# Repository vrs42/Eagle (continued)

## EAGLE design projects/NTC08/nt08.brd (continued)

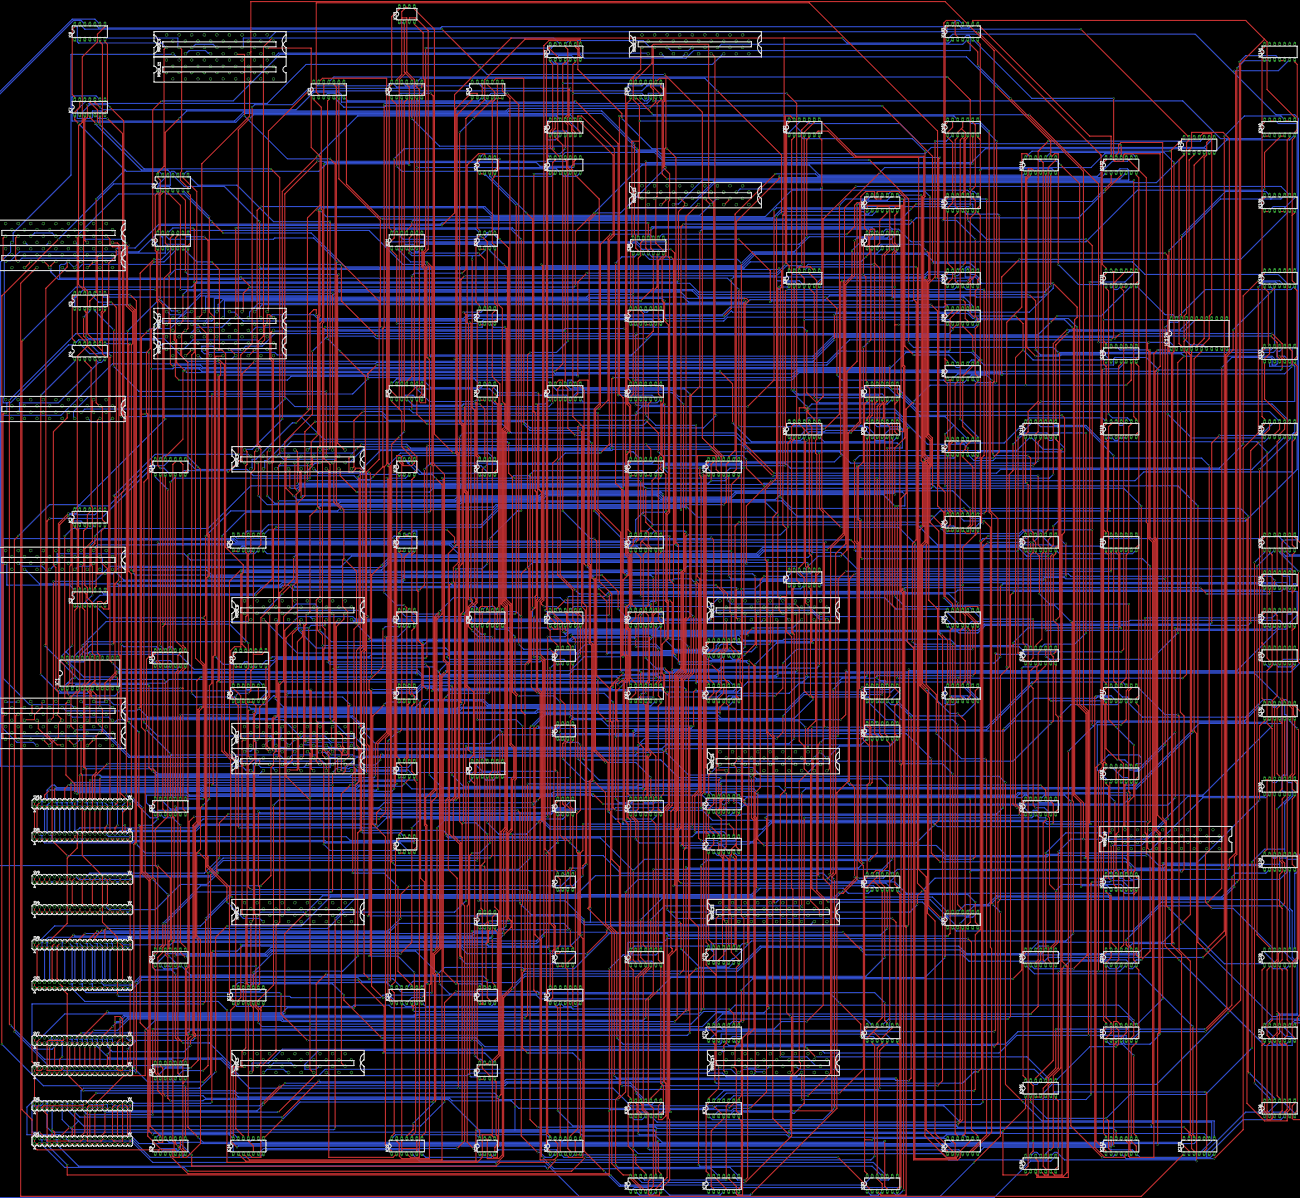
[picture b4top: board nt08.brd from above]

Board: 2 copper layers, 174 parts (0 on the bottom side), 550 nets.

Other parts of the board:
M916_11: W032; H807@1
M916_18: M228; H807@1

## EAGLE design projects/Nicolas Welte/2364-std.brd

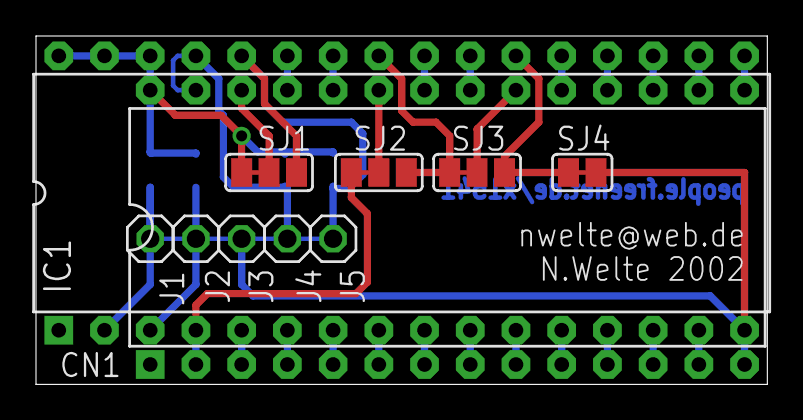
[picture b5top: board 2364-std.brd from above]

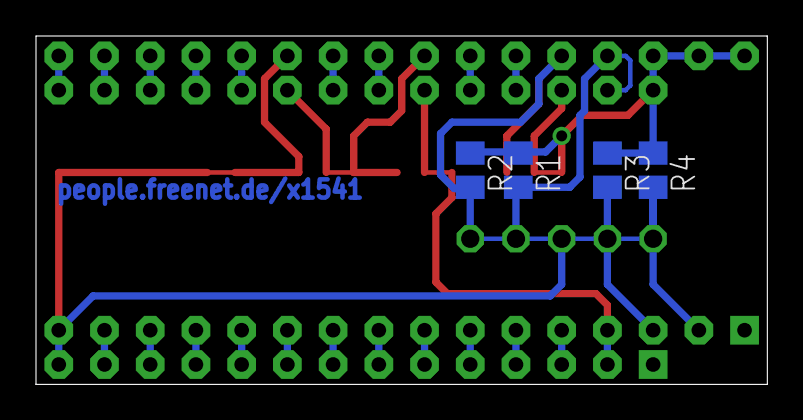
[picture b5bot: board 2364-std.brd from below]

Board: 2 copper layers, 40.6 x 19.4 mm, 15 parts (4 on the bottom side), 24 nets.

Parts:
CN1: DIL28-6
IC1: AT29C010; DIL32-3
J1, J2, J3, J4, J5: 1X01
R1, R2, R3, R4: M0805
SJ1, SJ2, SJ3: SJ_2
SJ4: SJ

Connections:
A0: CN1.10, IC1.12
A1: CN1.9, IC1.11
A2: CN1.8, IC1.10
A3: CN1.7, IC1.9
A4: CN1.6, IC1.8
A5: CN1.5, IC1.7
A6: CN1.4, IC1.6
A7: CN1.3, IC1.5
A8: CN1.25, IC1.27
A9: CN1.24, IC1.26
A10: CN1.21, IC1.23
A11: CN1.20, IC1.25, SJ2.3, SJ3.1, SJ3.2
A12: CN1.2, CN1.23, IC1.4, SJ2.1, SJ2.2
A13: CN1.14, CN1.27, IC1.2, IC1.3, IC1.16, IC1.22, IC1.28, IC1.29, J1.1, J2.1, J3.1, J4.1, J5.1, R1.2, R2.2, R3.2, R4.2, SJ1.3, SJ3.3, SJ4.1, SJ4.2
D0: CN1.11, IC1.13
D1: CN1.12, IC1.14
D2: CN1.13, IC1.15
D3: CN1.15, IC1.17
D4: CN1.16, IC1.18
D5: CN1.17, IC1.19
D6: CN1.18, IC1.20
D7: CN1.19, IC1.21
OE: CN1.22, IC1.24
VCC: CN1.26, CN1.28, IC1.30, IC1.31, IC1.32, R1.1, R2.1, R3.1, R4.1, SJ1.1, SJ1.2
